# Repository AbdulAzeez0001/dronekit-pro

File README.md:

# DroneKit Pro

**The programmable dual-boot PCB drone kit. Fly it with your phone. Code it in Python. Extend it with plug-in radio modules.**

DroneKit Pro is an open-hardware micro quadcopter kit built around a single pre-populated PCB frame. Flip the boot switch one way and it is a stable RC quad running Betaflight. Flip it the other way and it becomes a WiFi-connected programmable robot that runs your Python or Blockly code in the air.

Built for students, makers, teachers, and engineers.

> **Status:** Active development. The hardware design is not yet DRC-clean and the kit has not been physically built or flown. Do not order parts against this repo yet.

---

## The dual-boot idea

DroneKit Pro is two drones in one body:

- **Mode A (Fly)** — boot switch LOW. STM32F405 runs Betaflight, ESP32 off. Fly at 250Hz over ExpressLRS with full PID stabilisation.
- **Mode B (Code)** — boot switch HIGH. ESP32 opens a WiFi AP. Control from a browser at `192.168.4.1`, run Python via `dronekit_pcb`, or drag-and-drop Blockly. STM32 acts as motor co-processor.

---

## Specs (target)

| | |
|---|---|
| Frame | 130mm PCB-integrated, 1.6mm FR4 4-layer |
| Flight MCU | STM32F405RGT6 |
| Programmable MCU | ESP32-S3-WROOM-1-N8R2 (PSRAM, for the camera) |
| Camera | 24-pin DVP module (OV2640-class) on the ESP32-S3, WiFi video in Mode B |
| IMU / Baro | ICM-42688-P (SPI) / SPA06-003 (I2C) |
| Motors | 4x 8x20 brushed coreless (8 x 20mm, 15000 KV) |
| Motor drive | 4x AO3400A low-side MOSFET + SS54 flyback, brushed PWM (no ESC) |
| RX | Optional: any small serial ELRS receiver (user-supplied), CRSF on UART2 pads |
| Battery | 1S or 2S LiPo (board runs from either; 1S for the brushed whoop) |
| Build time | 3-4 hours (first build) |
| Target price | TBD - pending verified JLC/LCSC BOM quote |

> The original concept targeted ~50,000 NGN all-inclusive. That number is held as unverified until a real fab + BOM quote confirms it. See `docs/` for the cost analysis once generated.

---

## Repo layout

```
hardware/    KiCad project, gerbers, BOM, JLC fab files   (CERN-OHL-S)
firmware/    esp32/ + betaflight/ custom STM32F405 target  (MIT / GPLv3*)
software/    dronekit_pcb pip package + control-panel UI    (MIT)
simulation/  eCalc inputs, lightweight Python dynamics sim  (MIT)
docs/        kit documentation, assembly guide              (CC-BY-SA 4.0)
```

\* The Betaflight target is a derivative of Betaflight and is therefore GPLv3, regardless of the rest of the firmware.

---

## Licensing

This project is multi-licensed because hardware, software, and docs need different terms:

- **Hardware** (`hardware/`): CERN-OHL-S v2 — strongly reciprocal. See `LICENSE-hardware`.
- **Firmware + software** (`firmware/`, `software/`, `simulation/`): MIT, except the Betaflight target which is GPLv3. See `LICENSE-software`.
- **Documentation** (`docs/`): CC-BY-SA 4.0.

---

## Roadmap

- [ ] Dual-boot reset circuit verified on paper (datasheet-level, ESP32 strapping pins checked)
- [ ] Full schematic captured in KiCad
- [ ] PCB layout, ERC + DRC clean
- [ ] JLCPCB fab quote + LCSC BOM cost sheet
- [ ] Betaflight custom target for STM32F405
- [ ] ESP32 firmware: WiFi AP, control panel, WebSocket API, STM32 bridge
- [ ] `dronekit_pcb` Python package + simulated drone
- [ ] First physical board built and bench-tested
- [ ] First flight

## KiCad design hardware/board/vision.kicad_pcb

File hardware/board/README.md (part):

# Board — the blocks merged, then split into two stacked boards

`build_board.py` merges all ten circuit-as-code blocks into one system
schematic. Then it splits that into the two physical boards, **fc** (bottom)
and **vision** (top); see "Two boards" below. `build_pcb.py` starts each
board's PCB.

| File | What it is | Made by |
|---|---|---|
| `board.kicad_sch`, `board.net` | the whole system on one sheet: 155 parts, 116 nets. Reference only, no PCB | `build_board.py` |
| `fc.kicad_pro` / `.kicad_sch` / `.net` | flight-controller board: 105 parts incl. header J200 | `build_board.py` |
| `vision.kicad_pro` / `.kicad_sch` / `.net` | vision board: 52 parts incl. socket J201 | `build_board.py` |
| `fc.kicad_pcb`, `vision.kicad_pcb` | 4-layer 32 × 30 mm boards, both placed and routed | `build_pcb.py`, then the scripts below |
| `place_fc.py`, `place_vision.py` | each board's part placement (fixed spots + anchors) | by hand |
| `placer.py` | the placement engine both use | by hand |
| `route_setup.py`, `autoroute.py`, `fanout.py`, `handroute.py` | routing: net classes and pours, Freerouting, ground stitching, the rip-up router for what's left | by hand |
| `preroute_power.py`, `power_pour.py` | fc only: the battery and motor paths routed wide before everything else, then widened with pours and extra vias | by hand |
| `renders/` | KiCad 3D views of both sides of both boards | `kicad-cli pcb render` |
| `dronekit.pretty/` | custom footprints KiCad doesn't ship (TPS63070, M1.4 hole, wire pads, board-edge ESP32-S3) | `make_footprints.py` |
| `fp-lib-table` | points KiCad at `dronekit.pretty` (shared by both projects) | by hand |

**The schematics and netlists are generated, so don't hand-edit them.** Change the
block `.py` files and re-run the build. Rebuilds are deterministic: the same
blocks give byte-identical files, so git diffs show only real changes.

## Build

```
pip install skidl --break-system-packages
cd hardware/board
python3 build_board.py
```

Expected output ends with:

```
>>> 155 parts, 116 nets, 526 pins (28 unconnected)
>>> power flags on: GND, VBAT
>>> wrote board.net, board.kicad_sch, board.kicad_pro (whole system)
>>> schematic connectivity re-read from file: matches the netlist
>>> split: 17 nets cross on J200/J201: +3V3_ESP, +3V3_SYS, +3V8, ...
>>> fc    : 105 parts, 76 nets, power flags on GND, VBAT; wrote fc.net/.kicad_sch, re-read OK
>>> vision: 52 parts, 57 nets, power flags on +3V8, GND; wrote vision.net/.kicad_sch, re-read OK
```

## What the build does

1. **Runs every block script** in-process and collects its parts, pins and
   nets. It doesn't rewrite the block `.net` files.
2. **Replaces the stubs with one real STM32 (U1) and one real ESP32-S3
   (U2).**
   - Several blocks carry their own `U1`/`U2` stub with local pin numbers.
     The build keeps:
     - `U1` from `hardware/stm32`: STM32F405RGT6 LQFP64, with pins per ST
       DS8626, Figure 12.
     - A real `U2`: ESP32-S3-WROOM-1-N8R2, 41 pads per the Espressif
       datasheet v1.8, Table 3-1.
   - Every stub pin is checked against the real part. Its net must already
     be on the real pin of the same name, so a block wired to the wrong pin
     stops the build.
3. **Checks the result:**
   - no duplicate reference designators;
   - no net with a single connection;
   - no net with two power outputs.
4. **Writes the schematic:**
   - Each part gets a simple generated box symbol, embedded in the file.
   - Every connected pin gets a net label; parts connect by label name.
   - Every unused pin gets a no-connect flag.
   - Parts are grouped by block under a heading.
   - `PWR_FLAG`s go on GND and VBAT: nets with power inputs but no power
     output, so KiCad's ERC knows they're driven.
5. **Re-reads `board.kicad_sch`** and rebuilds the connectivity purely from
   pin and label coordinates, then confirms it matches the netlist exactly.
6. **Splits into fc and vision** (`BOARD_OF_BLOCK`, `BOARD_EXCEPTIONS`),
   adds J200/J201 with `B2B_PINOUT`, and checks the split:
   - every net with parts on both boards has a J200/J201 pin;
   - J200/J201 carry no net that doesn't need to cross.

   Then it writes, checks and re-reads each board's schematic as in steps
   3–5. `fc.kicad_pro` and `vision.kicad_pro` are written only if missing,
   so the design rules `build_pcb.py` puts in them survive a rebuild.

## Unconnected pins (all 28 are intentional)

| Part | Unused pins | Why |
|---|---|---|
| U1 STM32 | PC14, PC15, PC0, PC2, PC3, PA0, PA1, PC5, PB13–15, PA15, PC10–12, PD2, PB3 | spare: ADC pins + the SPI3 bank (see the pin map) |
| U2 ESP32-S3 | IO3, IO35–37 | IO3 is a strap (left floating on purpose); IO35–37 are spare on the N8R2 |
| U10 TPS63070 | FB2 | VSEL unused (single output voltage) |
| U11 RT9013 | NC | not connected inside the part |
| J90 USB-C | SBU1, SBU2 | not used by USB 2.0 |
| J30 camera FPC | Y0, Y1, NC | camera's 2 low data bits unused (8-bit mode) |

The ESP32-S3's programming pins are wired:

- **Native USB (IO19/IO20)** reaches the USB-C port through the TS3USB221A
  switch in Mode B.
- **UART0 (RXD0/TXD0)** goes to the J1 recovery pads.

See `hardware/stm32/stm32-design.md`.

## KiCad checks (KiCad 10.0.8, 2026-11-23)

- **ERC** on `board.kicad_sch`, `fc.kicad_sch` and `vision.kicad_sch`:
  0 errors. The only warnings say the `dronekit` symbol library isn't in
  KiCad's library table. The symbols are embedded in the schematics, so
  that's harmless.
- **Netlist:** KiCad's own netlist of `board.kicad_sch` has the same 116
  connected nets as `board.net`, pin for pin, plus one single-pin net for
  each of the 28 unused pins.
- **DRC** on `fc.kicad_pcb` and `vision.kicad_pcb`, with the schematic
  parity check: 0 violations and 0 parity issues on each. The unconnected
  items (fc 274, vision 141) are the ratsnest; nothing is routed yet.

```
"C:\Program Files\KiCad\10.0\bin\kicad-cli.exe" sch erc fc.kicad_sch
"C:\Program Files\KiCad\10.0\bin\kicad-cli.exe" pcb drc --schematic-parity fc.kicad_pcb
```
(same for `vision`).

## The PCB (`build_pcb.py`)

```
cd hardware/board
python make_footprints.py                                   # custom footprints
"C:\Program Files\KiCad\10.0\bin\python.exe" build_pcb.py fc       # needs KiCad's pcbnew
"C:\Program Files\KiCad\10.0\bin\python.exe" build_pcb.py vision
```

Both boards get the same:

- **Outline:** 32 × 30 mm with a 2 mm corner radius, centred at (150, 100)
  on the page. It matches `hardware/mechanical/fc_pcb_outline.dxf`; +X is the
  front, on the camera side.
- **Holes:** H1–H4, M1.4 (1.6 mm, not plated), on a 25.5 mm square. Each has
  a 3.6 mm keep-out on both sides for the standoffs.
- **Stackup:** 4 copper layers. fc is 0.8 mm thick (was 1.6 mm until
  2026-11-26; 0.8 mm saves 1.4 g, like most whoop FCs) and vision 1.0 mm. The plan is In1 = GND and
  In2 = power; neither plane is poured yet.
- **Rules:** set for JLCPCB's standard 4-layer process. Clearance and the
  smallest track are 0.1 mm, the default track is 0.15 mm, and vias are
  0.45 mm with a 0.2 mm drill. They're stored in `<board>.kicad_pro`.
- **Parts:** all are loaded with their nets and linked to their schematic
  symbols. The board-to-board pair is placed and locked; every other part is
  parked right of the board, one column per block.

**Re-running `build_pcb.py` overwrites `<board>.kicad_pcb`, including any
placement.** Once placement starts in KiCad, change the schematic with
`build_board.py`, then use **Tools > Update PCB from Schematic**.

Footprints that changed so the schematic fits KiCad 10's libraries:

- **TPS63070 (U10):** `dronekit:TI_RNM0015A_VQFN-HR-15_2.5x3mm_P0.5mm`,
  drawn from TI's land pattern (SLVSC58B, page 40). Re-check it against
  TI's current drawing before ordering.
- **TS3USB221A (U92):** KiCad's `Package_DFN_QFN:Texas_UQFN-10_1.5x2mm_P0.5mm`,
  which is TI's RSE0010A.
- **Inductor (L10):** `Inductor_SMD:L_Coilcraft_XxL4020`, the XFL/XAL4020
  footprint.
- **USB-C shield (J90):** the pad is named `SH` in KiCad's HRO footprint,
  not `S1`.

- **Wire pads** (battery J10, motors J40–J43, receiver J60, buzzer J120,
  SWD J91, ESP UART0 J1): plain SMD pads from `make_footprints.py`, with no
  paste because they're hand-soldered. They replace the through-hole
  pin-header placeholders, whose pins blocked both sides of the board.
  - Battery: 2.5 × 3.5 mm pads at 3.5 mm.
  - Motors and buzzer: 1.3 × 2.0 mm pads at 2.0 mm.
  - The rest: 1.0 × 1.8 mm pads at 1.5 mm.
- **Push buttons** SW90 (STM32 BOOT) and SW2 (ESP program): C&K KMR2,
  4.2 × 2.8 mm (`Button_Switch_SMD:SW_Push_1P1T_NO_CK_KMR2`), instead of
  the 6.2 × 6.2 mm SKQG. Same pin numbers.
- **Boot-mode switch** SW1: a 1-position slide switch you flip from above,
  the Copal CHS-01A (`SW_DIP_SPSTx01_Slide_Copal_CHS-01A_W5.08mm_P1.27mm_JPin`,
  7.3 × 3.3 mm). It replaces the side-lever PCM12 (8.9 × 5.9 mm), which
  had no edge space left on the vision board. It's the same 2-pin switch.
- **ESP32-S3 module (U2):** `dronekit:ESP32-S3-WROOM-1_BoardEdge`, made
  from KiCad's own footprint by `make_footprints.py`.
  - **Courtyard:** the module body only. KiCad's covers the 48 × 41 mm
    antenna clearance area, so every nearby part showed as a courtyard
    overlap.
  - **Keep-out:** trimmed to 21.8 mm across, so it ends just short of the
    two rear mounting holes. It still bans copper and parts on every layer
    beside the antenna.

Still to check: the ICM-42688-P footprint
`LGA-14_3x2.5mm_P0.5mm_LayoutBorder3x4y` against the datasheet land
pattern.

## Two boards (decided 2026-11-23)

The parts don't fit on one 32 × 30 mm board (see the area table below), so
the electronics are two boards with the same outline. They stack on the same
four M1.4 holes and are joined by one connector pair.

| Board | Where | What's on it | Parts' area |
|---|---|---|---|
| **fc** | bottom, 0.8 mm | power (battery, buck-boost, RT9013), STM32 + crystal, USB-C + ESD + USB switch, BOOT button, SWD, gyro, baro, motor drivers, buzzer, receiver port, the STM32's sensor-I²C and UART3 ports, the STM32 BOOT0/NRST parts | 1,150 mm² |
| **vision** | top, 1.0 mm | ESP32-S3-WROOM-1 + its AP7361C LDO, camera FPC and camera LDOs, boot-mode switch, ESP program button and UART0 pads, PWM and LED-strip ports, the ESP32-S3's I²C and IO ports | 1,206 mm² |

Each board has about 1,840 mm² on its two sides, so each is about 63 %
full. That's dense but buildable on 4 layers with parts on both sides.
(The areas are from before the smaller buttons and SMD wire pads; both
boards are a little emptier now.) If the vision board gets tight, these
swaps free the most room:

- the PCM12 slide switch SW1 for a smaller one;
- the SOT-223 LDO (U12) for an SOT-89 one;
- on fc, the four SMA flyback diodes for SOD-123FL ones.

## fc placement (`place_fc.py`, 2026-11-23)

(`renders/`: KiCad 3D views; the bottom view is seen from below, so it's
mirrored.)

```
"C:\Program Files\KiCad\10.0\bin\python.exe" build_pcb.py fc   # fresh board
"C:\Program Files\KiCad\10.0\bin\python.exe" place_fc.py        # place every part
```

The script places every part and is the record of why each one is where it
is. It refuses any courtyard overlap, keeps parts clear of the rounded
corners and the copper-to-edge rule, and lists every part it had to put
more than 4 mm from the pin it serves.

**Top**, which ends up under the vision board:

- **STM32:** in the middle, turned so that its USB, ESP32-S3, PWM and
  LED-strip pins (33–48) face J200.
- **Decoupling caps:** each at its supply pin.
- **Clock and boot:** the 8 MHz crystal at pins 5–6; the BOOT0, BOOT1, NRST
  and status-LED parts at their pins.
- **USB:** USB-C on the rear edge. The USBLC6 ESD chip sits between it and
  the TS3USB221A switch. The switch sits left of the band between the STM32
  and J200, next to J200's USB pins (7/8), so the band stays free for the
  STM32's escape wires. The two VCAP caps sit at the sides of that band for
  the same reason.
- **Front edge:** the sensor-I²C (J130) and UART3 (J131) JST-SH ports, with
  their series resistors.
- **Rear-left corner:** the RT9013 3.3 V LDO and the SPA06 baro.

**Bottom.** It's the only fc side you can reach with the vision board on,
so every wire pad is here.

- **Motors:** the four motor pad pairs sit at the corners, beside the
  mounting holes, where the wires come up from the pods. Each has its SS54
  diode and AO3400A FET right beside it:
  - the front diodes stand upright;
  - the rear ones lie flat, to clear the USB-C shell pins.
- **Buck-boost (left edge):** the TPS63070, with its inductor on the side
  of its L1/L2 pins, its input caps on the VIN side and its output caps on
  the VOUT side. It's about 9 mm from the gyro.
- **Battery input:** the battery pads, with the AO3401A reverse-polarity
  FET and the USB diode next to them.
- **Gyro:** the ICM-42688-P near the centre, next to the STM32's SPI1 pins,
  with its caps tight around it.
- **Other wire pads:** SWD, receiver and buzzer, with the buzzer's driver
  beside its pads.
- **BOOT button (KMR2):** at the front, pressable from below.

**Checks:** KiCad DRC reports 0 errors and 0 schematic-parity issues. The 45
warnings are all silkscreen: text clipped at the edge or overlapping a
neighbour's outline. Only the parts a builder solders or plugs into keep
their reference on the silkscreen; every other reference stays on the fab
layer. Routing: see "fc routing" below.

**Gyro orientation:** U80 sits at rotation 0 on the bottom, chip top facing
down, pin 1 at the rear-right corner seen from below. That puts the chip's
+X forward, +Y right and +Z down: a 180° roll flip from Betaflight's frame,
so `gyro_1_sensor_align = CW180FLIP`
(`firmware/betaflight/cli-defaults.txt`). This assumes InvenSense's usual
axis figure (pin 1 top-left, +X right, +Y up); TDK's datasheet could not be
fetched to confirm it. Bench-check the three axes in the Configurator before
the first flight (steps in that file).

## fc routing (2026-11-23, power paths redone 2026-11-24)

```
"C:\Program Files\KiCad.0in\python.exe" route_setup.py fc            # classes, pours, edge keep-out
"C:\Program Files\KiCad.0in\python.exe" preroute_power.py fc         # battery and motor paths first, wide
"C:\Program Files\KiCad.0in\python.exe" autoroute.py fc start --inner2  # Freerouting, detached
"C:\Program Files\KiCad.0in\python.exe" autoroute.py fc finish         # once .routing/fc.ses exists
"C:\Program Files\KiCad.0in\python.exe" fanout.py fc                   # a GND via in every floating ground island
"C:\Program Files\KiCad.0in\python.exe" handroute.py fc                # rip-up router for what's left
"C:\Program Files\KiCad.0in\python.exe" power_pour.py fc               # pours and extra vias along the power paths
```

**Result:** KiCad DRC reports 0 errors, 0 unconnected and 0 schematic-parity
issues. The 45 silkscreen warnings are the same as before. There are also 3
"dangling track" warnings: short stubs that the I2C clock line runs through,
so removing them breaks it. The board has 2852 track segments and 312 vias,
about 1.6 m of track: 736 mm on F.Cu, 417 mm on B.Cu and 450 mm on In2.Cu.
In1.Cu is a solid GND plane. In2.Cu is the +3V3_SYS pour, which signals also
cross where they have to.

### Power paths

The motors run straight off the battery: about 2.5 A per motor at full
throttle, about 10 A in all at the battery pads. The first routing left the
power nets the 0.8 mm the signals left free. One side's battery feed ran on
In2.Cu (0.5 oz, about 0.9 A at 0.8 mm) through a single via, which would have
overheated.

The power nets are now routed **first**, on the empty board
(`preroute_power.py`):

- **Layers and vias:** they use F.Cu and B.Cu only, since In2 is priced out.
  A layer change costs as much as 10 mm of track, and a path that needs more
  than 3 vias drops to the next narrower width.
- **Widths:**
  - the battery to J43: 2.0 mm;
  - then on to J42: 1.6 mm. That path runs down the right edge and around
    the bottom, and the other two motors branch off it (see the table
    below);
  - each motor's own branch and its negative to the FET: 1.0 mm (2.5 A);
  - the reverse-polarity FET and the buck-boost input: 0.8 mm.
- **Wider on the first try:** 2.5 mm everywhere left Freerouting 26
  connections short.

After the signals are routed, `power_pour.py` lays a copper pour along every
power track on F.Cu and B.Cu. The pours are wider than the track wherever
there is room. It also adds up to 6 more 0.6 / 0.3 mm vias around every power
via (17 in all), so no layer change carries the whole current through one
via.

The battery feed is a chain, not a star. From the battery pad (J10) it
runs down the right side to J43, down the right edge to J41, along the bottom
to J40 and up the left side to J42. Each stretch carries the motors still
ahead of it. The right edge, which carries three motors, has a second path
beside it: a 1.2 mm F.Cu track (19.5 mm) from the J43 junction to the J41
junction. It joins B.Cu through 2 vias at the top end and 3 at the bottom, and
takes about 2.9 A of the 7.5 A (the split follows the two paths' copper
resistance). A separate feed from the battery to the left motors doesn't fit:
the buck-boost on B.Cu and the parts on F.Cu leave no outer-layer path across
the top, even with signals ripped up, only one that runs 13 mm on In2. The copper width along each stretch is the track, or the pour
around it where that is wider (IPC-2221 temperature rise, all four motors at
2.5 A):

| Stretch | Carries | Narrowest copper | Rise, 1 oz outer | Rise, 2 oz outer |
|---|---|---|---|---|
| J10 pad to the J43 junction (B.Cu) | 10 A | 3.2 mm | about 38 °C | about 12 °C |
| right edge, J43 to J41 (B.Cu) | 4.6 A of the 7.5 A | 1.6 mm | about 20 °C | about 7 °C |
| right edge, parallel path (F.Cu) | 2.9 A of the 7.5 A | 1.1 mm | about 13 °C | about 4 °C |
| bottom, J41 to J40 (B.Cu) | 5 A | 1.77 mm | about 21 °C | about 7 °C |
| left side, J40 to J42 (F.Cu) | 2.5 A | 1.5 mm | about 6 °C | about 2 °C |
| each motor's negative, M1–M4_NEG | 2.5 A | 0.9 mm or more | about 13 °C | about 4 °C |

At JLCPCB's default 1 oz, every stretch but the first stays at about a
20 °C rise or less with all four motors at full throttle. The hottest is now
the 10 A stretch from the battery pad (about 38 °C). **2 oz outer copper**
brings every stretch to about 12 °C or less. IPC-2221 is cautious for
stretches this short, which shed heat into the pads and pours around them,
and 0802-size brushed motors usually draw less than 2.5 A.

**Fixes after the power pre-route:**

- **R15 battery-sense line:** Freerouting gave it the full VBAT_RAW width
  (0.8 mm), in a loop around the top of the STM32 that walled off the crystal
  and I2C pins. It carries no current, so it was ripped up and re-routed
  thin.
- **C16** (buck-boost VAUX cap): `place_fc.py` now turns it 180° (`TURN`),
  so its VAUX pad faces U10.3.
- **U10's VBAT feed:** it ran 0.15 mm under the BB_EN pin, so BB_EN could
  not get out. The feed was re-routed at 0.8 mm from the battery side.
- **Swapped rip-ups:** I2C1_SDA vs M4_PWM, and BEEPER vs LED0_K, kept
  ripping each other up. Each pair was closed by routing one with the other
  held fixed.
- **Right-edge parallel path** (added after the rest was routed): it ripped
  up BRIDGE_TX, ESP_USB_DP, I2C1_SCL, STM_BOOT0 and some GND stitching, and
  `handroute.py` re-routed them (LED_STRIP too, ripped on the way). The
  second via at its top end has a 1.45 mm B.Cu stub to the trunk: no spot
  near there has the net's pour on both layers.
- **Cleanup:** duplicate and overlapping copper left over from the
  hand-router rounds was removed, each piece only if DRC stayed clean
  without it.

The placement still rebuilds exactly (`build_pcb.py fc` + `place_fc.py`). The
routing doesn't: Freerouting isn't deterministic, and the fixes above were
made on the routed board.

**How it got there:**

- **Freerouting:** with the power paths routed first, it leaves 4
  connections. It runs to pass 999 and ignores its pass and time limits.
- **`fanout.py`:** puts a GND via in each ground-fill island on F.Cu and B.Cu
  that has no other way down to In1.
- **`handroute.py`:** a grid maze router (0.05 mm grid, F.Cu / In2.Cu / B.Cu)
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
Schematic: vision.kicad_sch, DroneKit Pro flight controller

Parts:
C1, C20: 10uF; C_0805_2012Metric
C2, C3, C34, C35, C36, C37: 100nF; C_0402_1005Metric
C19, C30, C31, C32, C33, C132, C133, C134, C135: 1uF; C_0402_1005Metric
J1: ESP_UART0; SolderPads_1x03_P1.5mm_1x1.8mm
J30: CAM_FPC_24P; Hirose_FH12-24S-0.5SH_1x24-1MP_P0.50mm_Horizontal
J132: LED_STRIP; JST_SH_SM03B-SRSS-TB_1x03-1MP_P1.00mm_Horizontal
J133: PWM; JST_SH_SM06B-SRSS-TB_1x06-1MP_P1.00mm_Horizontal
J134: CODE_I2C; JST_SH_SM04B-SRSS-TB_1x04-1MP_P1.00mm_Horizontal
J135: CODE_IO; JST_SH_SM06B-SRSS-TB_1x06-1MP_P1.00mm_Horizontal
J201: B2B_SOCKET_2x12_1.27mm; PinSocket_2x12_P1.27mm_Vertical
R1, R2, R4, R5, R6, R30, R33: 10k; R_0402_1005Metric
R31, R32, R141, R142: 4.7k; R_0402_1005Metric
R134, R135, R136, R137, R138, R139, R140, R143, R144, R145, R146: 100R; R_0402_1005Metric
SW1: boot_mode; SW_DIP_SPSTx01_Slide_Copal_CHS-01A_W5.08mm_P1.27mm_JPin
SW2: ESP_PROG; SW_Push_1P1T_NO_CK_KMR2
U2: ESP32-S3-WROOM-1-N8R2; ESP32-S3-WROOM-1_BoardEdge
U12: AP7361C-33E; SOT-223-3_TabPin2
U30: XC6206P282MR; SOT-23
U31: XC6206P122MR; SOT-23

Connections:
/+1V2_CAM: C33.1, C35.1, J30.15 (DVDD), U31.2 (VOUT)
/+2V8_CAM: C31.1, C36.1, J30.21 (AVDD), U30.2 (VOUT)
/+3V3_ESP: C1.1, C20.1, C30.1, C32.1, C34.1, C134.1, C135.1, J30.14 (DOVDD), J134.2 (3V3), J135.2 (3V3), J201.24 (+3V3_ESP_24), R4.2, R30.2, R31.2, R32.2, R33.2, R141.2, R142.2, U2.2 (3V3), U12.3 (OUT), U30.3 (VIN), U31.3 (VIN)
/+3V3_SYS: J201.23 (+3V3_SYS_23), R1.2
/+3V8: C19.1, C132.1, C133.1, J132.2 (PWR), J133.2 (PWR), J201.3 (+3V8_3), J201.4 (+3V8_4), J201.5 (+3V8_5), U12.1 (IN)
/BRIDGE_RX: J201.18 (BRIDGE_RX_18), U2.38 (IO2)
/BRIDGE_TX: J201.17 (BRIDGE_TX_17), U2.39 (IO1)
/CAM_HREF: J30.16 (HREF), U2.7 (IO7)
/CAM_PCLK: J30.8 (PCLK), U2.21 (IO13)
/CAM_PWDN: J30.17 (PWDN), R30.1, U2.22 (IO14)
/CAM_RESET: C37.1, J30.19 (RESET), R33.1
/CAM_SIOC: J30.20 (SIOC), R32.1, U2.5 (IO5)
/CAM_SIOD: J30.22 (SIOD), R31.1, U2.4 (IO4)
/CAM_VSYNC: J30.18 (VSYNC), U2.6 (IO6)
/CAM_XCLK: J30.12 (XCLK), U2.8 (IO15)
/CAM_Y2: J30.6 (Y2), U2.19 (IO11)
/CAM_Y3: J30.4 (Y3), U2.17 (IO9)
/CAM_Y4: J30.3 (Y4), U2.12 (IO8)
/CAM_Y5: J30.5 (Y5), U2.18 (IO10)
/CAM_Y6: J30.7 (Y6), U2.20 (IO12)
/CAM_Y7: J30.9 (Y7), U2.11 (IO18)
/CAM_Y8: J30.11 (Y8), U2.10 (IO17)
/CAM_Y9: J30.13 (Y9), U2.9 (IO16)
/ESP_EN: C3.1, J201.9 (ESP_EN_9), R2.1, U2.3 (EN)
/ESP_I2C_SCL: R140.1, R142.1, U2.25 (IO48)
/ESP_I2C_SDA: R139.1, R141.1, U2.24 (IO47)
/ESP_IO21: R143.1, U2.23 (IO21)
/ESP_IO38: R144.1, U2.31 (IO38)
/ESP_IO39: R145.1, U2.32 (IO39)
/ESP_IO40: R146.1, U2.33 (IO40)
/ESP_RXD0: J1.3 (RX), U2.36 (RXD0)
/ESP_TXD0: J1.2 (TX), U2.37 (TXD0)
/ESP_USB_DN: J201.8 (ESP_USB_DN_8), U2.13 (IO19)
/ESP_USB_DP: J201.7 (ESP_USB_DP_7), U2.14 (IO20)
/EXP_CODE_IO21: J135.3 (IO21), R143.2
/EXP_CODE_IO38: J135.4 (IO38), R144.2
/EXP_CODE_IO39: J135.5 (IO39), R145.2
/EXP_CODE_IO40: J135.6 (IO40), R146.2
/EXP_CODE_SCL: J134.4 (SCL), R140.2
/EXP_CODE_SDA: J134.3 (SDA), R139.2
/EXP_LED_DIN: J132.3 (DIN), R134.2
/EXP_PWM1: J133.3 (PWM1), R135.2
/EXP_PWM2: J133.4 (PWM2), R136.2
/EXP_PWM3: J133.5 (PWM3), R137.2
/EXP_PWM4: J133.6 (PWM4), R138.2
/GND: C1.2, C2.2, C3.2, C19.2, C20.2, C30.2, C31.2, C32.2, C33.2, C34.2, C35.2, C36.2, C37.2, C132.2, C133.2, C134.2, C135.2, J1.1 (GND), J30.10 (DGND), J30.23 (AGND), J132.1 (GND), J133.1 (GND), J134.1 (GND), J135.1 (GND), J201.1 (GND_1), J201.2 (GND_2), J201.6 (GND_6), J201.16 (GND_16), J201.19 (GND_19), J201.20 (GND_20), R2.2, R5.2, R6.2, SW1.2 (B), SW2.2 (B), U2.1 (GND), U2.40 (GND_40), U2.41 (EPAD), U12.2 (GND), U30.1 (VSS), U31.1 (VSS)
/LED_STRIP: J201.15 (LED_STRIP_15), R134.1
/MODE_SENSE: C2.1, J201.10 (MODE_SENSE_10), R1.1, SW1.1 (A)
/PWM1: J201.11 (PWM1_11), R135.1
/PWM2: J201.12 (PWM2_12), R136.1
/PWM3: J201.13 (PWM3_13), R137.1
/PWM4: J201.14 (PWM4_14), R138.1
/STM_BOOT0: J201.21 (STM_BOOT0_21), U2.34 (IO41)
/STM_NRST: J201.22 (STM_NRST_22), U2.35 (IO42)
/STRAP_IO0: R4.1, SW2.1 (A), U2.27 (IO0)
/STRAP_IO45: R5.1, U2.26 (IO45)
/STRAP_IO46: R6.1, U2.16 (IO46)

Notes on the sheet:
POWER: 1S/2S + USB -> buck-boost -> split 3.3 V rails
DUAL-BOOT: ESP32-S3 gating, bridge UART, straps
CAMERA: 24-pin DVP on the ESP32-S3
EXPANSION HEADERS
BOARD-TO-BOARD: fc J200 <-> vision J201
POWER FLAGS (tell ERC these nets are driven)

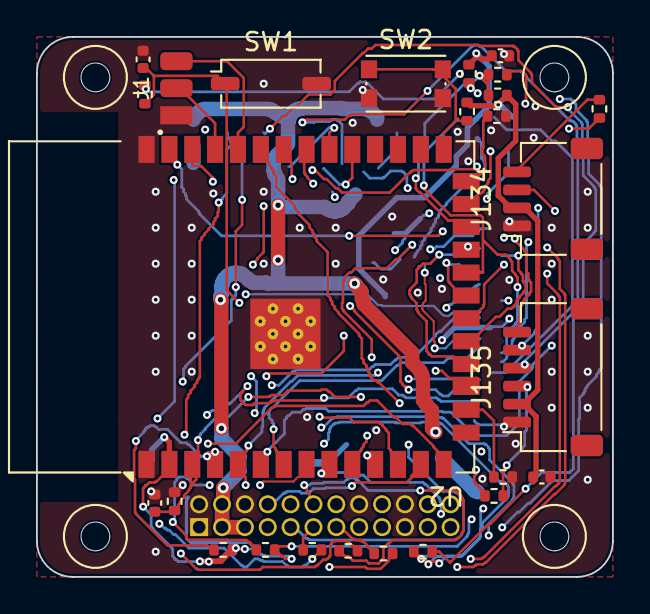
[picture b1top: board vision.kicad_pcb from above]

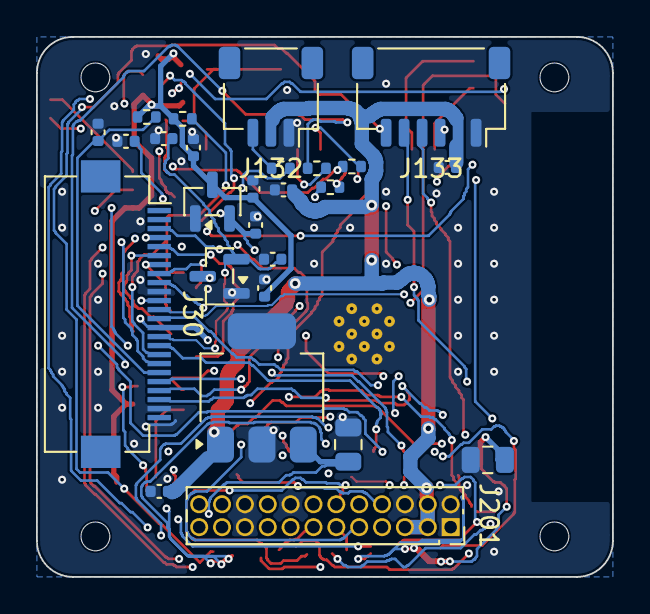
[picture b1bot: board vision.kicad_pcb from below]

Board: 4 copper layers, 32.0 x 30.0 mm, 56 parts (26 on the bottom side), 57 nets.

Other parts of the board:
H1, H2, H3, H4: M1.4; MountingHole_1.6mm_M1.4

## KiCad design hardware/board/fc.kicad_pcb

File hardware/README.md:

# Hardware

KiCad project for the DroneKit Pro PCB. Licensed CERN-OHL-S v2.

**Commit the sources** (`.kicad_sch`, `.kicad_pcb`, `.kicad_pro`), not just gerbers.
Gerbers are build output and are gitignored by default.

## How the design is organised

Each circuit block is written as code (SKiDL) in its own folder, with a design
doc that explains its choices:

| Folder | Block |
|---|---|
| `power/` | 1S/2S + USB power path -> TPS63070 buck-boost 3.8V -> RT9013 / AP7361C 3.3V |
| `stm32/` | STM32F405 flight MCU: supplies, crystal, USB-C, boot, SWD (master pin map) |
| `dual-boot/` | ESP32-S3-WROOM-1 gating, bridge UART, strapping pins |
| `gyro/` | ICM-42688-P on SPI1 |
| `baro/` | SPA06-003 barometer on I2C1 |
| `motors/` | 4 x brushed low-side MOSFET drivers |
| `camera/` | 24-pin DVP camera on the ESP32-S3 + its 2.8V/1.2V rails |
| `elrs/` | optional serial ELRS receiver port |
| `buzzer/` | Betaflight beeper |
| `expansion/` | six JST-SH expansion headers |
| `mechanical/` | cage / PCB outline (Fusion) |
| **`board/`** | **all blocks merged, then split into the two stacked boards (fc + vision): start here for KiCad** |

`stm32f405-pinmap.md` is the human-readable pin allocation.

## Workflow

1. Edit a block's `.py`, run it (ERC must be clean).
2. Run `board/build_board.py` to regenerate `board/board.kicad_sch`,
   `board/board.net` and the two boards' `fc.*` / `vision.*` (it cross-checks every shared pin and re-verifies the
   schematic's connectivity).
3. Run `board/build_pcb.py fc` and `board/build_pcb.py vision` with
   KiCad 10's Python to start the two stacked boards' PCBs (outline, holes,
   rules, board-to-board connector, every footprint with its nets), then
   `board/place_fc.py` and `board/place_vision.py` to place each board's
   parts. After that, change
   the schematic with `build_board.py` and use Tools > Update PCB from
   Schematic in KiCad, so placement and routing survive.
4. Clean DRC, then generate a JLCPCB fab quote and an LCSC BOM cost sheet
   (free, no purchase).

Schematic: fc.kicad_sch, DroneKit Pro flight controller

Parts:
C4, C16, C21, C61, C70, C71, C80, C90, C91, C92, C93, C95, C99, C103: 100nF; C_0402_1005Metric
C10, C11: 10uF/25V; C_0805_2012Metric
C12, C15: 10uF/25V; C_0603_1608Metric
C13, C14: 22uF/16V; C_0805_2012Metric
C17, C96, C102, C120, C130, C131: 1uF; C_0402_1005Metric
C18, C60: 10uF; C_0805_2012Metric
C40, C41: 22uF/25V; C_0805_2012Metric
C81, C97, C98: 2.2uF; C_0603_1608Metric
C82: 10nF; C_0402_1005Metric
C94: 4.7uF; C_0603_1608Metric
C100, C101: 20pF; C_0402_1005Metric
D10, D120: B5819W; D_SOD-123
D40, D41, D42, D43: SS54; D_SMA
D90: LED_blue; LED_0402_1005Metric
J10: VBAT_1S_2S; SolderPads_1x02_P3.5mm_2.5x3.5mm
J40: M1; SolderPads_1x02_P2mm_1.3x2mm
J41: M2; SolderPads_1x02_P2mm_1.3x2mm
J42: M3; SolderPads_1x02_P2mm_1.3x2mm
J43: M4; SolderPads_1x02_P2mm_1.3x2mm
J60: ELRS_RX; SolderPads_1x04_P1.5mm_1x1.8mm
J90: USB-C; USB_C_Receptacle_HRO_TYPE-C-31-M-12
J91: SWD; SolderPads_1x05_P1.5mm_1x1.8mm
J120: BUZZER; SolderPads_1x02_P2mm_1.3x2mm
J130: SENSOR_I2C; JST_SH_SM04B-SRSS-TB_1x04-1MP_P1.00mm_Horizontal
J131: UART3; JST_SH_SM04B-SRSS-TB_1x04-1MP_P1.00mm_Horizontal
J200: B2B_HEADER_2x12_1.27mm; PinHeader_2x12_P1.27mm_Vertical
L10: 1.5uH; L_Coilcraft_XxL4020
Q10: AO3401A; SOT-23
Q40, Q41, Q42, Q43, Q120: AO3400A; SOT-23
R3, R15, R44, R45, R46, R47, R80, R93, R121: 10k; R_0402_1005Metric
R10, R12, R13, R14: 100k; R_0402_1005Metric
R11: 374k; R_0402_1005Metric
R16, R17, R92, R94: 1k; R_0402_1005Metric
R40, R41, R42, R43, R120: 22R; R_0402_1005Metric
R60, R61, R130, R131, R132, R133: 100R; R_0402_1005Metric
R70, R71, R90, R91: 5.1k; R_0402_1005Metric
SW90: BOOT; SW_Push_1P1T_NO_CK_KMR2
U1: STM32F405RGT6; LQFP-64_10x10mm_P0.5mm
U10: TPS63070RNM; TI_RNM0015A_VQFN-HR-15_2.5x3mm_P0.5mm
U11: RT9013-33GB; SOT-23-5
U70: SPA06-003; Bosch_LGA-8_2x2.5mm_P0.65mm_ClockwisePinNumbering
U80: ICM-42688-P; LGA-14_3x2.5mm_P0.5mm_LayoutBorder3x4y
U91: USBLC6-2SC6; SOT-23-6
U92: TS3USB221A; Texas_UQFN-10_1.5x2mm_P0.5mm
Y90: 8MHz CL=20pF; Crystal_SMD_3225-4Pin_3.2x2.5mm

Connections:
/+3V3_ESP: C130.1, J130.2 (3V3), J200.24 (+3V3_ESP_24)
/+3V3_SYS: C18.1, C70.1, C71.1, C80.1, C81.1, C82.1, C90.1, C91.1, C92.1, C93.1, C94.1, C95.1, C96.1, C99.1, C103.1, J91.1 (3V3), J200.23 (+3V3_SYS_23), R70.2, R71.2, R80.2, R94.2, SW90.2 (B), U1.1 (VBAT), U1.13 (VDDA), U1.19 (VDD_19), U1.32 (VDD_32), U1.48 (VDD_48), U1.64 (VDD_64), U11.5 (VOUT), U70.2 (CSB), U70.6 (VDDIO), U70.8 (VDD), U80.5 (VDDIO), U80.8 (VDD), U92.10 (VCC)
/+3V8: C13.1, C14.1, C15.1, C17.1, C60.1, C61.1, C120.1, C131.1, D120.1 (K), J60.2 (PWR), J120.1 (BZ+), J131.2 (PWR), J200.3 (+3V8_3), J200.4 (+3V8_4), J200.5 (+3V8_5), R11.1, R14.2, U10.7 (VOUT), U10.8 (VOUT_2), U11.1 (VIN), U11.3 (EN)
/BB_EN: R13.1, U10.14 (EN)
/BB_FB: R11.2, R12.1, U10.5 (FB)
/BB_L1: L10.1, U10.11 (L1)
/BB_L2: L10.2, U10.9 (L2)
/BB_VAUX: C16.1, U10.3 (VAUX)
/BEEPER: R120.1, U1.61 (PB8)
/BOOT1: R93.1, U1.28 (PB2)
/BOOT_BTN: R92.1, SW90.1 (A)
/BRIDGE_RX: J200.18 (BRIDGE_RX_18), U1.43 (PA10)
/BRIDGE_TX: J200.17 (BRIDGE_TX_17), U1.42 (PA9)
/BZ_GATE: Q120.1 (G), R120.2, R121.1
/BZ_NEG: D120.2 (A), J120.2 (BZ-), Q120.3 (D)
/CRSF_RX: J60.4 (FC_RX), R61.2
/CRSF_RX_MCU: R61.1, U1.17 (PA3)
/CRSF_TX: J60.3 (FC_TX), R60.2
/CRSF_TX_MCU: R60.1, U1.16 (PA2)
/ESP_EN: J200.9 (ESP_EN_9), U1.33 (PB12)
/ESP_USB_DN: J200.8 (ESP_USB_DN_8), U92.4 (2D-)
/ESP_USB_DP: J200.7 (ESP_USB_DP_7), U92.3 (2D+)
/EXP_SENSOR_SCL: J130.4 (SCL), R131.2
/EXP_SENSOR_SDA: J130.3 (SDA), R130.2
/EXP_UART3_RX: J131.4 (RX), R133.2
/EXP_UART3_TX: J131.3 (TX), R132.2
/GND: C4.2, C10.2, C11.2, C12.2, C13.2, C14.2, C15.2, C16.2, C17.2, C18.2, C21.2, C40.2, C41.2, C60.2, C61.2, C70.2, C71.2, C80.2, C81.2, C82.2, C90.2, C91.2, C92.2, C93.2, C94.2, C95.2, C96.2, C97.2, C98.2, C99.2, C100.2, C101.2, C102.2, C103.2, C120.2, C130.2, C131.2, J10.2 (GND), J60.1 (GND), J90.A1 (GND_A1), J90.A12 (GND_A12), J90.B1 (GND_B1), J90.B12 (GND_B12), J90.SH (SHIELD), J91.5 (GND), J130.1 (GND), J131.1 (GND), J200.1 (GND_1), J200.2 (GND_2), J200.6 (GND_6), J200.16 (GND_16), J200.19 (GND_19), J200.20 (GND_20), Q40.2 (S), Q41.2 (S), Q42.2 (S), Q43.2 (S), Q120.2 (S), R3.2, R10.2, R12.2, R16.2, R44.2, R45.2, R46.2, R47.2, R90.2, R91.2, R93.2, R121.2, U1.12 (VSSA), U1.18 (VSS_18), U1.63 (VSS_63), U10.1 (PS/SYNC), U10.4 (GND), U10.10 (PGND), U10.15 (VSEL), U11.2 (GND), U70.1 (GND), U70.5 (SDO), U70.7 (GND_7), U80.2 (RESV_2), U80.3 (RESV_3), U80.6 (GND), U80.7 (RESV_7), U80.9 (INT2), U80.10 (RESV_10), U80.11 (RESV_11), U91.2 (GND), U92.5 (GND), U92.6 (OE), Y90.2 (GND), Y90.4 (GND_4)
/GYRO_CS: R80.1, U1.20 (PA4), U80.12 (AP_CS)
/GYRO_INT: U1.24 (PC4), U80.4 (INT1)
/GYRO_MISO: U1.22 (PA6), U80.1 (AP_SDO)
/GYRO_MOSI: U1.23 (PA7), U80.14 (AP_SDI)
/GYRO_SCK: U1.21 (PA5), U80.13 (AP_SCLK)
/I2C1_SCL: R70.1, R131.1, U1.58 (PB6), U70.4 (SCK)
/I2C1_SDA: R71.1, R130.1, U1.59 (PB7), U70.3 (SDA)
/LED0_A: D90.2 (A), R94.1
/LED0_K: D90.1 (K), U1.62 (PB9)
/LED_STRIP: J200.15 (LED_STRIP_15), U1.41 (PA8)
/M1_GATE: Q40.1 (G), R40.2, R44.1
/M1_NEG: D40.2 (A), J40.2 (M-), Q40.3 (D)
/M1_PWM: R40.1, U1.26 (PB0)
/M2_GATE: Q41.1 (G), R41.2, R45.1
/M2_NEG: D41.2 (A), J41.2 (M-), Q41.3 (D)
/M2_PWM: R41.1, U1.27 (PB1)
/M3_GATE: Q42.1 (G), R42.2, R46.1
/M3_NEG: D42.2 (A), J42.2 (M-), Q42.3 (D)
/M3_PWM: R42.1, U1.56 (PB4)
/M4_GATE: Q43.1 (G), R43.2, R47.1
/M4_NEG: D43.2 (A), J43.2 (M-), Q43.3 (D)
/M4_PWM: R43.1, U1.57 (PB5)
/MODE_SENSE: J200.10 (MODE_SENSE_10), U1.2 (PC13), U92.9 (S)
/OSC_IN: C100.1, U1.5 (PH0), Y90.1
/OSC_OUT: C101.1, U1.6 (PH1), Y90.3
/PG_3V8: R14.1, U10.2 (PG)
/PWM1: J200.11 (PWM1_11), U1.37 (PC6)
/PWM2: J200.12 (PWM2_12), U1.38 (PC7)
/PWM3: J200.13 (PWM3_13), U1.39 (PC8)
/PWM4: J200.14 (PWM4_14), U1.40 (PC9)
/Q10_GATE: Q10.1 (G), R10.1, R17.2
/STM_BOOT0: J200.21 (STM_BOOT0_21), R3.1, R92.2, U1.60 (BOOT0)
/STM_NRST: C4.1, J91.4 (NRST), J200.22 (STM_NRST_22), U1.7 (NRST)
/STM_USB_DN: U1.44 (PA11), U92.2 (1D-)
/STM_USB_DP: U1.45 (PA12), U92.1 (1D+)
/SWCLK: J91.3 (SWCLK), U1.49 (PA14)
/SWDIO: J91.2 (SWDIO), U1.46 (PA13)
/UART3_RX: R133.1, U1.30 (PB11)
/UART3_TX: R132.1, U1.29 (PB10)
/USB_CC1: J90.A5 (CC1), R90.1
/USB_CC2: J90.B5 (CC2), R91.1
/USB_DN: J90.A7 (DN_A7), J90.B7 (DN_B7), U91.3 (IO2), U91.4 (IO2_4), U92.7 (D-)
/USB_DP: J90.A6 (DP_A6), J90.B6 (DP_B6), U91.1 (IO1), U91.6 (IO1_6), U92.8 (D+)
/VBAT: C10.1, C11.1, C12.1, D10.1 (K), Q10.2 (S), R13.2, U10.12 (VIN), U10.13 (VIN_2)
/VBAT_RAW: C40.1, C41.1, D40.1 (K), D41.1 (K), D42.1 (K), D43.1 (K), J10.1 (VBAT), J40.1 (M+), J41.1 (M+), J42.1 (M+), J43.1 (M+), Q10.3 (D), R15.1
/VBAT_SENSE: C21.1, R15.2, R16.1, U1.9 (PC1)
/VBUS: C102.1, D10.2 (A), J90.A4 (VBUS_A4), J90.A9 (VBUS_A9), J90.B4 (VBUS_B4), J90.B9 (VBUS_B9), R17.1, U91.5 (VBUS)
/VCAP_1: C97.1, U1.31 (VCAP_1)
/VCAP_2: C98.1, U1.47 (VCAP_2)

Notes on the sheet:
POWER: 1S/2S + USB -> buck-boost -> split 3.3 V rails
FLIGHT MCU: STM32F405 + crystal, USB-C, boot, SWD
DUAL-BOOT: ESP32-S3 gating, bridge UART, straps
GYRO: ICM-42688-P on SPI1
BARO: SPA06-003 on I2C1
MOTORS: 4 x brushed low-side MOSFET
RC RECEIVER PORT (optional ELRS add-on)
BUZZER: Betaflight beeper
EXPANSION HEADERS
BOARD-TO-BOARD: fc J200 <-> vision J201
POWER FLAGS (tell ERC these nets are driven)

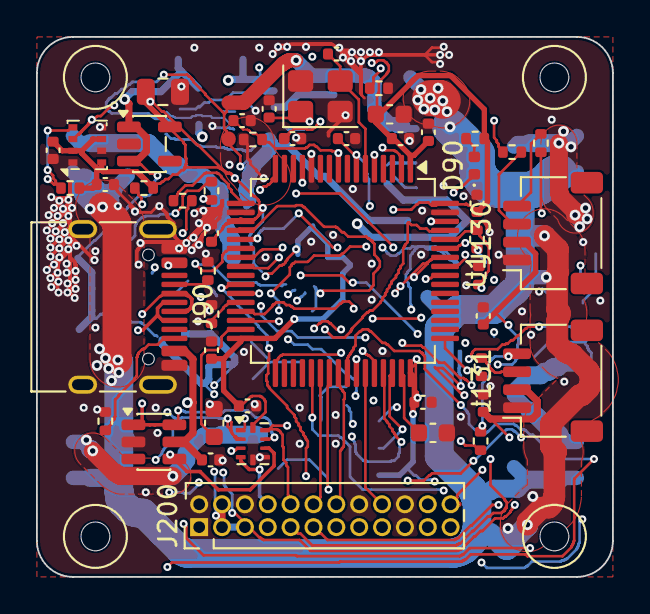
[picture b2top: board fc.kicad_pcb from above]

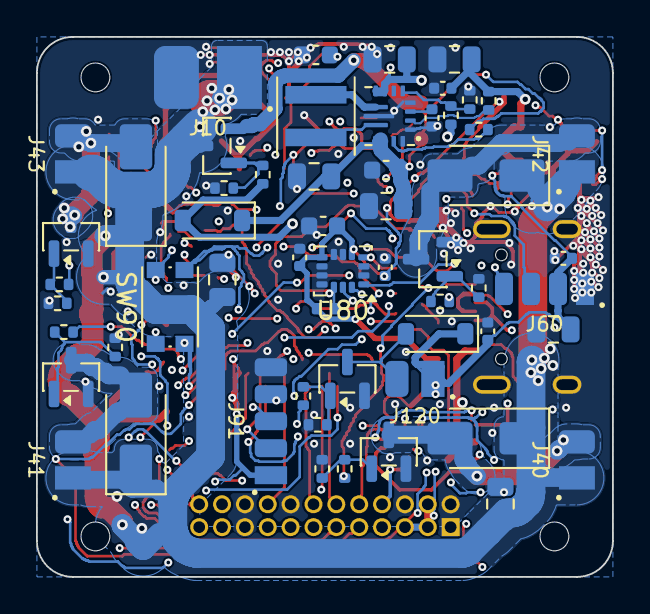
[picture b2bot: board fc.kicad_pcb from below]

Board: 4 copper layers, 32.0 x 30.0 mm, 109 parts (57 on the bottom side), 76 nets.

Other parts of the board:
H1, H2, H3, H4: M1.4; MountingHole_1.6mm_M1.4

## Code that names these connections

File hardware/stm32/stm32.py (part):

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
Decisions encoded here:
  1. 8 MHz HSE crystal: what Betaflight's STM32F405 targets expect.
  2. USB-C, USB 2.0 full-speed (PA11/PA12). VBUS goes to the power block's
     USB power path (Schottky + battery-FET gate drive), which powers the
     logic without back-feeding the LiPo; motors never run from USB.
     The data lines go through a TS3USB221A USB 2.0 switch steered by the
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     CC1/CC2 5.1k pull-downs so USB-C hosts see a device; USBLC6-2SC6 ESD
     protection on D+/D-.
  3. BOOT button to 3.3V through 1k: holds BOOT0 high for DFU. The 1k
     protects the ESP32-S3 GPIO41 that also drives BOOT0 (STM_BOOT0 net,
     10k pull-down in the dual-boot block).
  4. PB2/BOOT1 pulled down (10k): system-memory boot needs BOOT1 = 0.
  5. SWD pads (3V3, SWDIO, SWCLK, NRST, GND) for debugging/recovery.
  6. Status LED on PB9 (Betaflight LED0), active low.

Refs are PINNED in a reserved 90-119 range so this block never collides with
dual-boot (auto), power (10-29), camera (30-39), motors (40-59), receiver
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# STM32F405RGT6, LQFP64 - all 64 pins, numbers per DS8626 Figure 12.
# ----------------------------------------------------------------------------
LQFP64 = {
     1: "VBAT",  2: "PC13",  3: "PC14",  4: "PC15",  5: "PH0",   6: "PH1",
     7: "NRST",  8: "PC0",   9: "PC1",  10: "PC2",  11: "PC3",  12: "VSSA",
    13: "VDDA", 14: "PA0",  15: "PA1",  16: "PA2",  17: "PA3",  18: "VSS_18",
    19: "VDD_19", 20: "PA4", 21: "PA5", 22: "PA6",  23: "PA7",  24: "PC4",
    25: "PC5",  26: "PB0",  27: "PB1",  28: "PB2",  29: "PB10", 30: "PB11",
    31: "VCAP_1", 32: "VDD_32", 33: "PB12", 34: "PB13", 35: "PB14", 36: "PB15",
    37: "PC6",  38: "PC7",  39: "PC8",  40: "PC9",  41: "PA8",  42: "PA9",
    43: "PA10", 44: "PA11", 45: "PA12", 46: "PA13", 47: "VCAP_2", 48: "VDD_48",
    49: "PA14", 50: "PA15", 51: "PC10", 52: "PC11", 53: "PC12", 54: "PD2",
    55: "PB3",  56: "PB4",  57: "PB5",  58: "PB6",  59: "PB7",  60: "BOOT0",
    61: "PB8",  62: "PB9",  63: "VSS_63", 64: "VDD_64",
}
POWER_PINS = {"VBAT", "VSSA", "VDDA", "VSS_18", "VDD_19", "VDD_32", "VDD_48",
              "VSS_63", "VDD_64"}
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c98 = Cn("C98", "2.2uF", C0603); vcap2 += u1["VCAP_2"], c98[1]; gnd += c98[2]

# ----------------------------------------------------------------------------
# 8 MHz HSE crystal on PH0/PH1
# ----------------------------------------------------------------------------
osc_in = Net("OSC_IN"); osc_out = Net("OSC_OUT")
osc_in  += u1["PH0"], y90["1"]
osc_out += u1["PH1"], y90["3"]
gnd += y90["GND"], y90["GND_4"]
c100 = Cn("C100", "20pF"); osc_in  += c100[1]; gnd += c100[2]
c101 = Cn("C101", "20pF"); osc_out += c101[1]; gnd += c101[2]
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usb_dn += j90["DN_A7"], j90["DN_B7"], u91["IO2"], u91["IO2_4"], u92["D-"]

# Port 1 -> STM32 (Mode A), port 2 -> ESP32-S3 native USB (Mode B)
stm_dp = Net("STM_USB_DP"); stm_dp += u92["1D+"], u1["PA12"]
stm_dn = Net("STM_USB_DN"); stm_dn += u92["1D-"], u1["PA11"]
esp_dp = Net("ESP_USB_DP"); esp_dp += u92["2D+"], esp["IO20"]
esp_dn = Net("ESP_USB_DN"); esp_dn += u92["2D-"], esp["IO19"]

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# ----------------------------------------------------------------------------
# Boot: BOOT0 button (DFU) and BOOT1 pull-down
# ----------------------------------------------------------------------------
stm_boot0 = Net("STM_BOOT0")            # dual-boot block: 10k pull-down + ESP32-S3 GPIO41
stm_boot0 += u1["BOOT0"]
r92 = Rn("R92", "1k")                   # protects ESP32-S3 GPIO41 when the button is held
btn = Net("BOOT_BTN"); btn += sw90["A"], r92[1]
stm_boot0 += r92[2]
v3v3_sys  += sw90["B"]

r93 = Rn("R93", "10k")                  # PB2/BOOT1 low: system-memory boot when BOOT0 = 1
boot1 = Net("BOOT1"); boot1 += u1["PB2"], r93[1]; gnd += r93[2]

stm_nrst = Net("STM_NRST")              # dual-boot block: 100nF + ESP32-S3 GPIO42 (open drain)
stm_nrst += u1["NRST"]

# ----------------------------------------------------------------------------
# SWD pads + status LED
# ----------------------------------------------------------------------------
swdio = Net("SWDIO"); swdio += u1["PA13"], j91["SWDIO"]
swclk = Net("SWCLK"); swclk += u1["PA14"], j91["SWCLK"]
stm_nrst += j91["NRST"]
v3v3_sys += j91["3V3"]; gnd += j91["GND"]

r94 = Rn("R94", "1k")                   # LED0 (Betaflight), active low
led = Net("LED0_K"); led += d90["K"], u1["PB9"]
led_a = Net("LED0_A"); led_a += d90["A"], r94[1]; v3v3_sys += r94[2]

# ----------------------------------------------------------------------------
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# ----------------------------------------------------------------------------
BLOCK_NETS = {
    # dual-boot (hardware/dual-boot)
    "PC13": "MODE_SENSE", "PB12": "ESP_EN", "PA9": "BRIDGE_TX", "PA10": "BRIDGE_RX",
    # gyro (hardware/gyro)
    "PA5": "GYRO_SCK", "PA6": "GYRO_MISO", "PA7": "GYRO_MOSI",
    "PA4": "GYRO_CS", "PC4": "GYRO_INT",
    # baro (hardware/baro)
    "PB6": "I2C1_SCL", "PB7": "I2C1_SDA",
    # receiver port (hardware/elrs)
    "PA2": "CRSF_TX_MCU", "PA3": "CRSF_RX_MCU",
    # motors (hardware/motors)
    "PB0": "M1_PWM", "PB1": "M2_PWM", "PB4": "M3_PWM", "PB5": "M4_PWM",
    # power (hardware/power)
    "PC1": "VBAT_SENSE",
    # buzzer (hardware/buzzer)
    "PB8": "BEEPER",
    # expansion headers (hardware/expansion)
    "PB10": "UART3_TX", "PB11": "UART3_RX", "PA8": "LED_STRIP",
    "PC6": "PWM1", "PC7": "PWM2", "PC8": "PWM3", "PC9": "PWM4",
}
for pin, net in BLOCK_NETS.items():
    n = Net.fetch(net); n += u1[pin]     # reuse the net if this block already made it
    n.do_erc = False        # other end lives in that block's netlist (merged by name)

# Every remaining GPIO is free (expansion) - mark explicitly unconnected.
used = set(BLOCK_NETS) | {"PH0", "PH1", "PA11", "PA12", "PA13", "PA14", "PB2",
                          "PB9", "BOOT0", "NRST", "VCAP_1", "VCAP_2"} | POWER_PINS
for n, name in LQFP64.items():
    if name not in used:
        u1[name].func = T.NOCONNECT
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
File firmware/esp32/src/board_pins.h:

// DroneKit Pro vision board: ESP32-S3-WROOM-1 pins (MIT).
// Checked against hardware/board/vision.kicad_pcb on 2026-11-24.
#pragma once

// UART bridge to the STM32 (Betaflight MSP on its UART1, 115200).
constexpr int PIN_BRIDGE_RX = 1;    // module pad 39, net BRIDGE_TX (STM32 PA9 -> here)
constexpr int PIN_BRIDGE_TX = 2;    // module pad 38, net BRIDGE_RX (here -> STM32 PA10)
constexpr unsigned long BRIDGE_BAUD = 115200;

// STM32 flash control. Left alone in normal running:
//   BOOT0 driven low (it also has a 10k pull-down on fc),
//   NRST released (high impedance; the STM32 has its own pull-up).
constexpr int PIN_STM_BOOT0 = 41;   // module pad 34
constexpr int PIN_STM_NRST = 42;    // module pad 35

// Expansion headers (all through 100R).
constexpr int PIN_CODE_I2C_SDA = 47; // J134, 4.7k pull-ups on the board
constexpr int PIN_CODE_I2C_SCL = 48;
constexpr int PIN_CODE_IO21 = 21;    // J135
constexpr int PIN_CODE_IO38 = 38;
constexpr int PIN_CODE_IO39 = 39;
constexpr int PIN_CODE_IO40 = 40;

// Camera (OV2640 on J30) - not used yet. The Y2..Y9 order depends on the
// J30 connector's contact side, which isn't confirmed. See
// hardware/camera/camera-design.md before using these.
constexpr int PIN_CAM_SIOD = 4;
constexpr int PIN_CAM_SIOC = 5;
constexpr int PIN_CAM_VSYNC = 6;
constexpr int PIN_CAM_HREF = 7;
constexpr int PIN_CAM_XCLK = 15;
constexpr int PIN_CAM_PCLK = 13;
constexpr int PIN_CAM_PWDN = 14;
constexpr int PIN_CAM_Y2 = 11;
constexpr int PIN_CAM_Y3 = 9;
constexpr int PIN_CAM_Y4 = 8;
constexpr int PIN_CAM_Y5 = 10;
constexpr int PIN_CAM_Y6 = 12;
constexpr int PIN_CAM_Y7 = 18;
constexpr int PIN_CAM_Y8 = 17;
constexpr int PIN_CAM_Y9 = 16;

// Never drive the strapping pins GPIO0/3/45/46 (hardware/dual-boot/).

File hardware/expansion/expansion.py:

"""
DroneKit Pro - expansion headers block, as code.

Six small JST-SH (1.0 mm) headers for plug-in modules. Four hang off the
STM32 (flight side, Mode A / Betaflight); two hang off the ESP32-S3 (student
code side, Mode B):

  J130 SENSOR   STM32 I2C1 (shared with the baro)   Qwiic/STEMMA QT pin order
  J131 UART3    STM32 USART3 PB10/PB11              GPS, optical flow, telemetry
  J132 LED      STM32 PA8 (TIM1_CH1)                WS2812 LED strip
  J133 PWM      STM32 PC6-PC9 (TIM8_CH1-4)          servos, gripper, extra outputs
  J134 CODE-I2C ESP32-S3 GPIO47/48                  Qwiic/STEMMA QT pin order
  J135 CODE-IO  ESP32-S3 GPIO21/38/39/40            digital I/O, PWM, one-wire

Design reference: hardware/expansion/expansion-design.md

Decisions encoded here:
  1. Split by MCU. In Mode B the student's code runs on the ESP32-S3, so its
     modules plug into ESP pins directly. Flight add-ons (GPS, flow, LEDs)
     need Betaflight, so they go to the STM32.
  2. Both I2C headers use the Qwiic / STEMMA QT pin order (GND, 3V3, SDA,
     SCL) on a 4-pin JST-SH, so off-the-shelf Qwiic sensors plug straight in.
  3. 3.3 V header power comes from +3V3_ESP (1 A LDO with margin), NOT the
     gyro's +3V3_SYS. +3V8 (no 5 V on the board) feeds the UART, LED and PWM
     headers for modules with their own regulators / WS2812 LEDs.
  4. 100R series resistor on every signal pin: protects MCU pins from
     students' wiring mistakes and hot-plugging.
  5. I2C pull-ups: J130 shares I2C1, whose pull-ups already sit in the baro
     block; J134 gets its own 4.7k pull-ups to +3V3_ESP.
  6. Local 1uF decoupling on each header's power pin.

U1 = the STM32 (same as the stm32 block's U1); U2 = the ESP32-S3 (same as
dual-boot U2). Only the pins used here are listed, with local pin numbers.
Refs are PINNED in a reserved 130-159 range so this block never collides with
any other block.
Run:  python3 expansion.py   ->  writes expansion.net + prints ERC.
"""

from skidl import Part, Pin, Net, SKIDL, KICAD8, TEMPLATE, generate_netlist, ERC, set_default_tool

set_default_tool(SKIDL)
T = Pin.types

R = Part(name="R", tool=SKIDL, ref_prefix="R", dest=TEMPLATE,
         footprint="Resistor_SMD:R_0402_1005Metric",
         pins=[Pin(num=1, name="1", func=T.PASSIVE),
               Pin(num=2, name="2", func=T.PASSIVE)])

C = Part(name="C", tool=SKIDL, ref_prefix="C", dest=TEMPLATE,
         footprint="Capacitor_SMD:C_0402_1005Metric",
         pins=[Pin(num=1, name="1", func=T.PASSIVE),
               Pin(num=2, name="2", func=T.PASSIVE)])

_ref = {"R": 130, "C": 130}
def Rn(value):
    p = R(value=value); p.ref = f"R{_ref['R']}"; _ref["R"] += 1; return p
def Cn(value):
    p = C(value=value); p.ref = f"C{_ref['C']}"; _ref["C"] += 1; return p

def SH(ref, label, names):
    n = len(names)
    p = Part(name=f"JST_SH_{n}P", tool=SKIDL, ref_prefix="J", dest=TEMPLATE,
             pins=[Pin(num=i + 1, name=nm, func=T.PASSIVE) for i, nm in enumerate(names)]
             )(value=label,
               footprint=f"Connector_JST:JST_SH_SM{n:02d}B-SRSS-TB_1x{n:02d}-1MP_P1.00mm_Horizontal")
    p.ref = ref
    return p

# ----------------------------------------------------------------------------
# MCU stubs (local pin numbers)
# ----------------------------------------------------------------------------
STM_PINS = ["PB6", "PB7", "PB10", "PB11", "PA8", "PC6", "PC7", "PC8", "PC9"]
stm32 = Part(name="STM32F405RGT6", tool=SKIDL, ref_prefix="U", dest=TEMPLATE,
             pins=[Pin(num=1, name="VSS", func=T.PWRIN)] +
                  [Pin(num=2 + i, name=p, func=T.BIDIR) for i, p in enumerate(STM_PINS)]
             )(value="STM32F405RGT6", footprint="Package_QFP:LQFP-64_10x10mm_P0.5mm")
stm32.ref = "U1"

ESP_PINS = ["IO47", "IO48", "IO21", "IO38", "IO39", "IO40"]
esp = Part(name="ESP32-S3-WROOM-1-N8R2", tool=SKIDL, ref_prefix="U", dest=TEMPLATE,
           pins=[Pin(num=1, name="3V3", func=T.PWRIN), Pin(num=2, name="GND", func=T.PWRIN)] +
                [Pin(num=3 + i, name=p, func=T.BIDIR) for i, p in enumerate(ESP_PINS)]
           )(value="ESP32-S3-WROOM-1-N8R2", footprint="RF_Module:ESP32-S3-WROOM-1")
esp.ref = "U2"

# ----------------------------------------------------------------------------
# Power
# ----------------------------------------------------------------------------
v3v3_esp = Net("+3V3_ESP"); v3v3_esp.drive = Pin.drives.POWER   # from power block (AP7361C)
v3v8     = Net("+3V8");     v3v8.drive     = Pin.drives.POWER   # from power block (TPS63070)
gnd      = Net("GND");      gnd.drive      = Pin.drives.POWER
gnd += stm32["VSS"], esp["GND"]
v3v3_esp += esp["3V3"]

def signal(mcu_pin, header_pin, mcu_net, hdr_net):
    """MCU pin -> 100R -> header pin."""
    r = Rn("100R")
    a = Net(mcu_net); a += mcu_pin, r[1]
    b = Net(hdr_net); b += r[2], header_pin
    return a, b

# J130 SENSOR: STM32 I2C1 (pull-ups live in the baro block). Qwiic order.
j130 = SH("J130", "SENSOR_I2C", ["GND", "3V3", "SDA", "SCL"])
gnd += j130["GND"]; v3v3_esp += j130["3V3"]
c = Cn("1uF"); v3v3_esp += c[1]; gnd += c[2]
signal(stm32["PB7"], j130["SDA"], "I2C1_SDA", "EXP_SENSOR_SDA")
signal(stm32["PB6"], j130["SCL"], "I2C1_SCL", "EXP_SENSOR_SCL")

# J131 UART3: GPS / optical flow / telemetry
j131 = SH("J131", "UART3", ["GND", "PWR", "TX", "RX"])
gnd += j131["GND"]; v3v8 += j131["PWR"]
c = Cn("1uF"); v3v8 += c[1]; gnd += c[2]
signal(stm32["PB10"], j131["TX"], "UART3_TX", "EXP_UART3_TX")   # STM32 TX -> module RX
signal(stm32["PB11"], j131["RX"], "UART3_RX", "EXP_UART3_RX")   # STM32 RX <- module TX

# J132 LED: WS2812 strip on PA8 (TIM1_CH1)
j132 = SH("J132", "LED_STRIP", ["GND", "PWR", "DIN"])
gnd += j132["GND"]; v3v8 += j132["PWR"]
c = Cn("1uF"); v3v8 += c[1]; gnd += c[2]
signal(stm32["PA8"], j132["DIN"], "LED_STRIP", "EXP_LED_DIN")

# J133 PWM: TIM8 CH1-4 on PC6-PC9
j133 = SH("J133", "PWM", ["GND", "PWR", "PWM1", "PWM2", "PWM3", "PWM4"])
gnd += j133["GND"]; v3v8 += j133["PWR"]
c = Cn("1uF"); v3v8 += c[1]; gnd += c[2]
for i, pin in enumerate(["PC6", "PC7", "PC8", "PC9"]):
    signal(stm32[pin], j133[f"PWM{i + 1}"], f"PWM{i + 1}", f"EXP_PWM{i + 1}")

# J134 CODE-I2C: ESP32-S3 GPIO47 (SDA) / GPIO48 (SCL), own pull-ups. Qwiic order.
j134 = SH("J134", "CODE_I2C", ["GND", "3V3", "SDA", "SCL"])
gnd += j134["GND"]; v3v3_esp += j134["3V3"]
c = Cn("1uF"); v3v3_esp += c[1]; gnd += c[2]
sda, _ = signal(esp["IO47"], j134["SDA"], "ESP_I2C_SDA", "EXP_CODE_SDA")
scl, _ = signal(esp["IO48"], j134["SCL"], "ESP_I2C_SCL", "EXP_CODE_SCL")
r = Rn("4.7k"); sda += r[1]; v3v3_esp += r[2]
r = Rn("4.7k"); scl += r[1]; v3v3_esp += r[2]

# J135 CODE-IO: ESP32-S3 GPIO21/38/39/40
j135 = SH("J135", "CODE_IO", ["GND", "3V3", "IO21", "IO38", "IO39", "IO40"])
gnd += j135["GND"]; v3v3_esp += j135["3V3"]
c = Cn("1uF"); v3v3_esp += c[1]; gnd += c[2]
for io in ["IO21", "IO38", "IO39", "IO40"]:
    signal(esp[io], j135[io], f"ESP_{io}", f"EXP_CODE_{io}")

ERC()
generate_netlist(tool=KICAD8, file_="expansion.net")
print(">>> wrote expansion.net")
